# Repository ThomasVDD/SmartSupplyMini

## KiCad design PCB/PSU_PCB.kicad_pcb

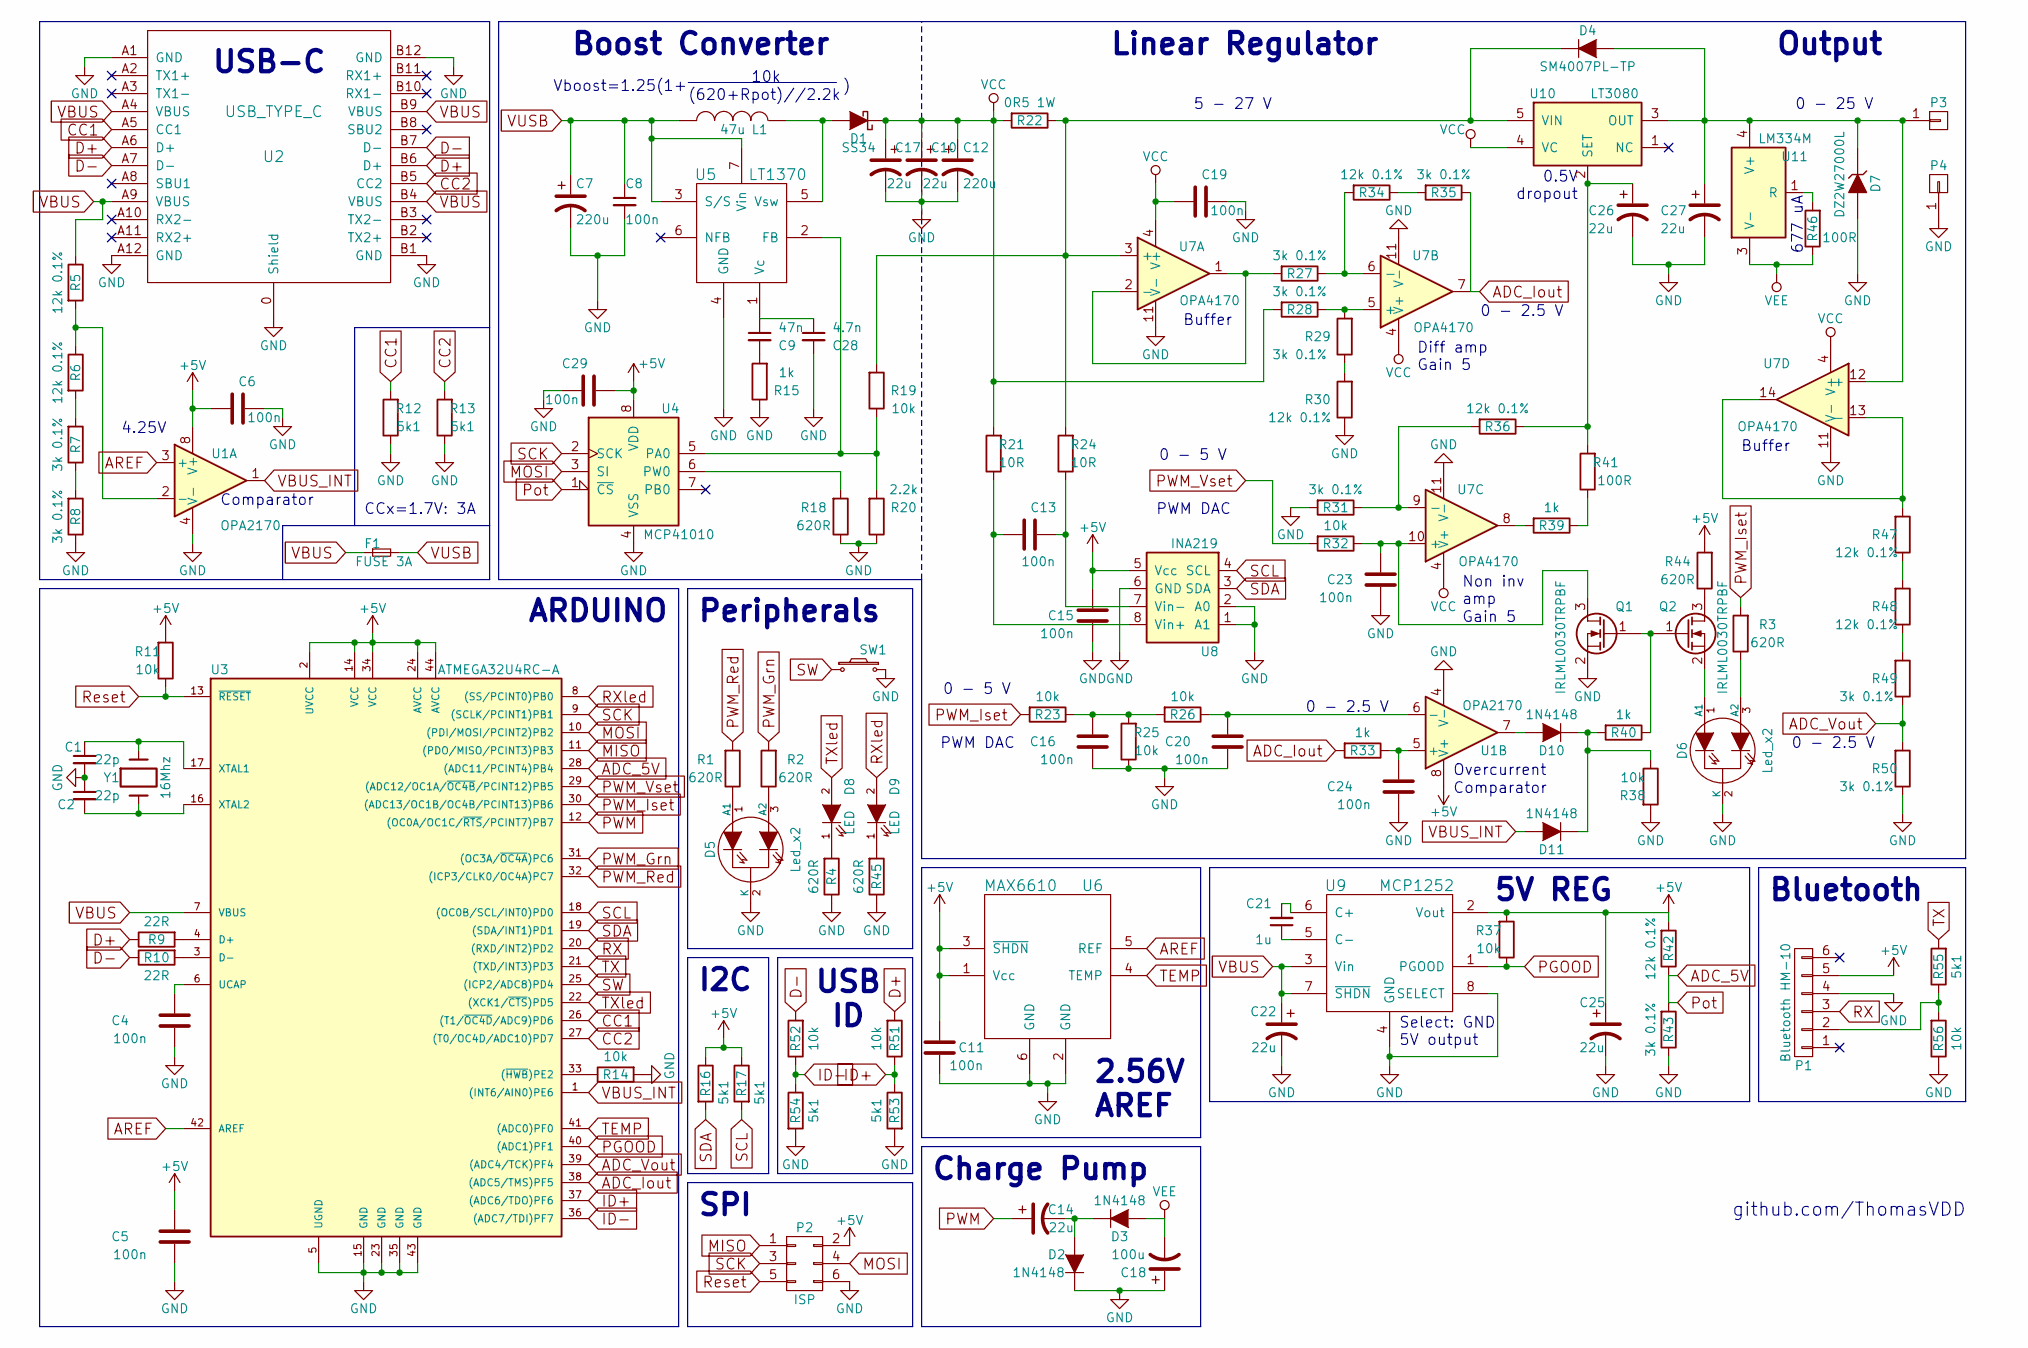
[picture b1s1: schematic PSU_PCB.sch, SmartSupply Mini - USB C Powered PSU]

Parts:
C1, C2: 22p; C_0603_HandSoldering
C4, C5, C6, C8, C11, C13, C15, C16, C19, C20, C23, C24, C29: 100n; C_0603_HandSoldering
C7, C12: 220u; CP_Elec_6.3x7.7
C9: 47n; C_0603_HandSoldering
C10, C17, C27: 22u; CP_Tantalum_Case-V_EIA-7343-20_Hand
C14: 22u; CP_Elec_6.3x7.7
C18: 100u; CP_Elec_6.3x7.7
C21: 1u; C_0603_HandSoldering
C22, C25, C26: 22u; C_0805_HandSoldering
C28: 4.7n; C_0603_HandSoldering
D1: SS34; D_SMC_Handsoldering
D2, D3, D10, D11: 1N4148; D_SOD-323_HandSoldering
D4: SM4007PL-TP; D_SOD-123F
D5, D6: Led_x2; LED_Rectangular_W5.0mm_H2.0mm-3pins
D7: DZ2W27000L; D_SOD-123F
D8, D9: LED; LED_0603_HandSoldering
F1: FUSE 3A; R_0603_HandSoldering
L1: 47u; SELF-WE-PD-XXL
P1: Bluetooth HM-10; Pin_Header_Straight_1x06_Pitch2.54mm
P2: ISP; Pin_Header_Straight_2x03_Pitch2.54mm
P3: V+; BananaPad
P4: V-; BananaPad
Q1, Q2: IRLML0030TRPBF; SOT-23
R1, R2, R3, R4, R18, R44, R45: 620R; R_0603_HandSoldering
R5, R6, R30, R34, R36, R42, R47, R48: 12k 0.1%; R_0603_HandSoldering
R7, R8, R27, R28, R29, R31, R35, R43, R49, R50: 3k 0.1%; R_0603_HandSoldering
R9, R10: 22R; R_0603_HandSoldering
R11, R14, R19, R23, R25, R26, R32, R37, R38, R51, R52, R56: 10k; R_0603_HandSoldering
R12, R13, R16, R17, R53, R54, R55: 5k1; R_0603_HandSoldering
R15, R33, R39, R40: 1k; R_0603_HandSoldering
R20: 2.2k; R_0603_HandSoldering
R21, R24: 10R; R_0603_HandSoldering
R22: 0R5 1W; R_2512_HandSoldering
R41, R46: 100R; R_0603_HandSoldering
SW1: SW_PUSH_SMALL_H; SW_Tactile_SKHH_Angled
U1: OPA2170; SOIC-8_3.9x4.9mm_Pitch1.27mm
U2: USB_TYPE_C; USB_C_Connector
U3: ATMEGA32U4RC-A; TQFP-44_10x10mm_Pitch0.8mm
U4: MCP41010; SOIC-8_3.9x4.9mm_Pitch1.27mm
U5: LT1370; TO-263-7_TabPin4
U6: MAX6610; SOT-23-6_Handsoldering
U7: OPA4170; SOIC-14_3.9x8.7mm_Pitch1.27mm
U8: INA219; SOIC-8_3.9x4.9mm_Pitch1.27mm
U9: MCP1252; MSOP-8_3x3mm_Pitch0.65mm
U10: LT3080; TO-263-5_TabPin3
U11: LM334M; SOIC-8_3.9x4.9mm_Pitch1.27mm
Y1: 16Mhz; Crystal_SMD_HC49-SD_HandSoldering

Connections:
+5V: C5.2, C6.2, C11.1, C15.1, C25.1, C29.2, P1.5, P2.2, R11.2, R16.1, R17.1, R37.2, R42.2, R44.2, U1.8 (V+), U3.2 (UVCC), U3.14 (VCC), U3.24 (AVCC), U3.34 (VCC), U3.44 (AVCC), U4.8 (VDD), U6.1 (Vcc), U6.3 (~SHDN), U8.5 (Vcc), U9.2 (Vout)
ADC_5V: R42.1, R43.2, U3.28 ((ADC11/PCINT4)PB4), U4.1 (~CS)
ADC_Iout: R33.2, R35.1, U3.38 ((ADC5/TMS)PF5), U7.7
ADC_Vout: R49.1, R50.2, U3.39 ((ADC4/TCK)PF4)
AREF: U1.3 (+), U3.42 (AREF), U6.5 (REF)
CC1: R12.2, U2.A5 (CC1), U3.26 ((T1/~OC4D~/ADC9)PD6)
CC2: R13.2, U2.B5 (CC2), U3.27 ((T0/OC4D/ADC10)PD7)
D+: R9.1, R51.2, U2.A6 (D+), U2.B6 (D+)
D-: R10.1, R52.2, U2.A7 (D-), U2.B7 (D-)
GND: C1.2, C2.1, C4.1, C5.1, C6.1, C7.2, C8.2, C10.2, C11.2, C12.2, C15.2, C16.1, C17.2, C18.1, C19.1, C20.1, C22.2, C23.1, C24.1, C25.2, C26.2, C27.2, C28.2, C29.1, D2.1 (K), D5.2 (K), D6.2 (K), D7.2 (A), P1.4, P2.6, P4.1, Q1.2 (S), R4.1, R8.1, R12.1, R13.1, R14.2, R15.1, R18.1, R20.1, R25.1, R30.1, R31.2, R38.2, R43.1, R45.1, R50.1, R53.2, R54.2, R56.1, SW1.2, U1.4 (V-), U2.0 (Shield), U2.A1 (GND), U2.A12 (GND), U2.B1 (GND), U2.B12 (GND), U3.5 (UGND), U3.15 (GND), U3.23 (GND), U3.35 (GND), U3.43 (GND), U4.4 (VSS), U5.4 (GND), U6.2 (GND), U6.6 (GND), U7.11 (V-), U8.1 (A1), U8.2 (A0), U8.6 (GND), U9.4 (GND), U9.8 (SELECT)
ID+: R51.1, R53.1, U3.37 ((ADC6/TDO)PF6)
ID-: R52.1, R54.1, U3.36 ((ADC7/TDI)PF7)
MISO: P2.1, U3.11 ((PDO/MISO/PCINT3)PB3)
MOSI: P2.4, U3.10 ((PDI/MOSI/PCINT2)PB2), U4.3 (SI)
unnamed: C1.1, U3.17 (XTAL1), Y1.1
unnamed: C2.2, U3.16 (XTAL2), Y1.2
unnamed: C4.2, U3.6 (UCAP)
unnamed: C9.2, R15.2
unnamed: C13.1, R24.1, U8.7 (Vin-)
unnamed: C13.2, R21.1, U8.8 (Vin+)
unnamed: C14.2, D2.2 (A), D3.1 (K)
unnamed: C16.2, R23.1, R25.2, R26.2
unnamed: C20.2, R26.1, U1.6 (-)
unnamed: C21.1, U9.5 (C-)
unnamed: C21.2, U9.6 (C+)
unnamed: C23.2, Q1.3 (D), R32.1, U7.10 (+)
unnamed: C24.2, R33.1, U1.5 (+)
unnamed: C26.1, R36.1, R41.2, U10.2 (SET)
unnamed: C27.1, D4.2 (A), D7.1 (K), P3.1, U7.12 (+), U10.3 (OUT), U11.4 (V+)
unnamed: C9.1, C28.1, U5.1 (Vc)
unnamed: D1.2 (A), L1.1, U5.5 (Vsw)
unnamed: D4.1 (K), R19.2, R22.1, R24.2, U7.3 (+), U10.5 (VIN)
unnamed: D5.1 (A1), R1.1
unnamed: D5.3 (A2), R2.1
unnamed: D6.1 (A1), Q2.2 (S)
unnamed: D6.3 (A2), R3.1
unnamed: D8.1 (K), R4.2
unnamed: D9.1 (K), R45.2
unnamed: D10.1 (K), D11.1 (K), R38.1, R40.2
unnamed: D10.2 (A), U1.7
unnamed: P1.2, R55.1, R56.2
unnamed: Q1.1 (G), Q2.1 (G), R40.1
unnamed: Q2.3 (D), R44.1
unnamed: R5.2, R6.1, U1.2 (-)
unnamed: R6.2, R7.2
unnamed: R7.1, R8.2
unnamed: R9.2, U3.4 (D+)
unnamed: R10.2, U3.3 (D-)
unnamed: R14.1, U3.33 ((~HWB~)PE2)
unnamed: R18.2, U4.6 (PW0)
unnamed: R19.1, R20.2, U4.5 (PA0), U5.2 (FB)
unnamed: R27.1, R34.2, U7.6 (-)
unnamed: R27.2, U7.1, U7.2 (-)
unnamed: R28.1, R29.2, U7.5 (+)
unnamed: R29.1, R30.2
unnamed: R31.1, R36.2, U7.9 (-)
unnamed: R34.1, R35.2
unnamed: R39.1, R41.1
unnamed: R39.2, U7.8
unnamed: R46.2, U11.1 (R)
unnamed: R47.1, R48.2
unnamed: R47.2, U7.13 (-), U7.14
unnamed: R48.1, R49.2
PGOOD: R37.1, U3.40 ((ADC1)PF1), U9.1 (PGOOD)
PWM: C14.1, U3.12 ((OC0A/OC1C/~RTS~/PCINT7)PB7)
PWM_Grn: R2.2, U3.31 ((OC3A/~OC4A~)PC6)
PWM_Iset: R3.2, R23.2, U3.30 ((ADC13/OC1B/OC4B/PCINT13)PB6)
PWM_Red: R1.2, U3.32 ((ICP3/CLK0/OC4A)PC7)
PWM_Vset: R32.2, U3.29 ((ADC12/OC1A/~OC4B~/PCINT12)PB5)
RX: P1.3, U3.20 ((RXD/INT2)PD2)
RXled: D9.2 (A), U3.8 ((SS/PCINT0)PB0)
Reset: P2.5, R11.1, U3.13 (~RESET~)
SCK: P2.3, U3.9 ((SCLK/PCINT1)PB1), U4.2 (SCK)
SCL: R17.2, U3.18 ((OC0B/SCL/INT0)PD0), U8.4 (SCL)
SDA: R16.2, U3.19 ((SDA/INT1)PD1), U8.3 (SDA)
SW: SW1.1, U3.25 ((ICP2/ADC8)PD4)
TEMP: U3.41 ((ADC0)PF0), U6.4 (TEMP)
TX: R55.2, U3.21 ((TXD/INT3)PD3)
TXled: D8.2 (A), U3.22 ((XCK1/~CTS~)PD5)
VBUS: C22.1, F1.1, R5.1, U2.A4 (VBUS), U2.A9 (VBUS), U2.B4 (VBUS), U2.B9 (VBUS), U3.7 (VBUS), U9.3 (Vin), U9.7 (~SHDN)
VBUS_INT: D11.2 (A), U1.1, U3.1 ((INT6/AIN0)PE6)
VCC: C10.1, C12.1, C17.1, C19.2, D1.1 (K), R21.2, R22.2, R28.2, U7.4 (V+), U10.4 (VC)
VEE: C18.2, D3.2 (A), R46.1, U11.3 (V-)
VUSB: C7.1, C8.1, F1.2, L1.2, U5.3 (S/S), U5.7 (Vin)

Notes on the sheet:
677 uA
Charge Pump
5V REG
0 - 5 V
0 - 2.5 V
Buffer
Diff amp Gain 5
Comparator
PWM DAC
Non inv amp
Gain 5
0 - 25 V
5 - 27 V
Boost Converter
github.com/ThomasVDD
Vboost=1.25(1+ )
10k
(620+Rpot)//2.2k
__________________
USB-C
ARDUINO
I2C
SPI
Select: GND 5V output
2.56V AREF
Linear Regulator
Output
Peripherals
4.25V
Bluetooth
USB ID
CCx=1.7V: 3A
Overcurrent
0.5V dropout

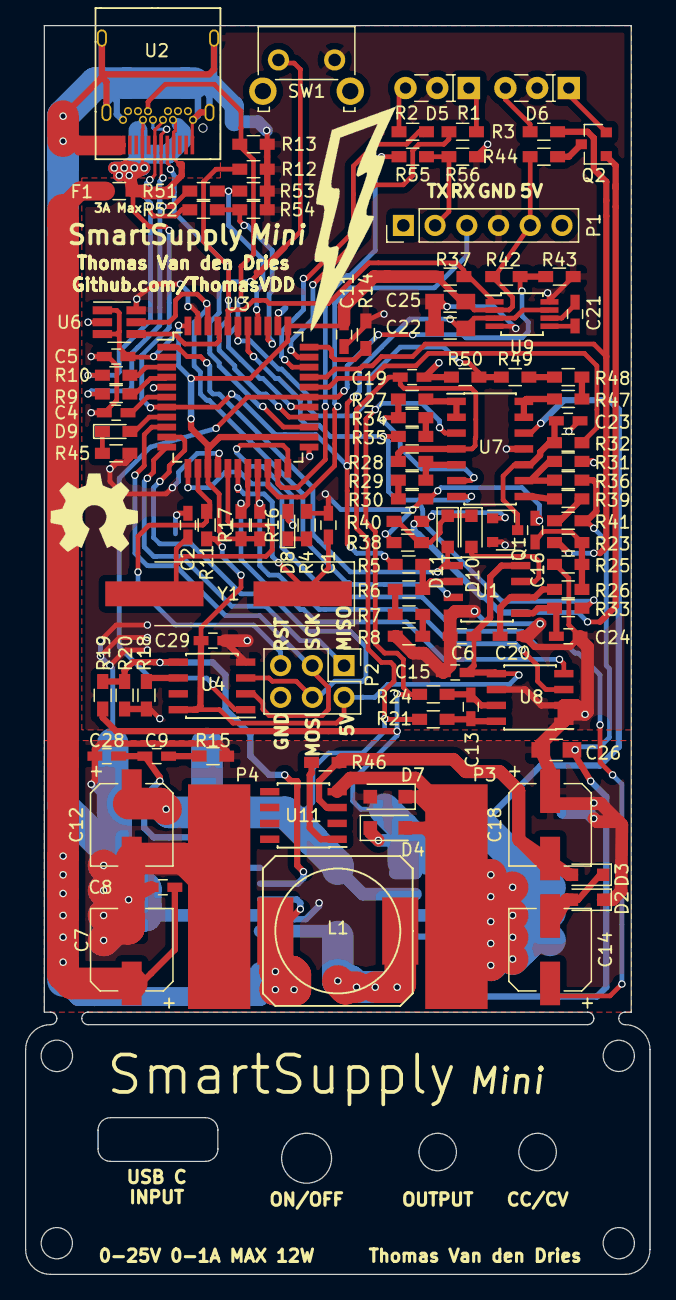
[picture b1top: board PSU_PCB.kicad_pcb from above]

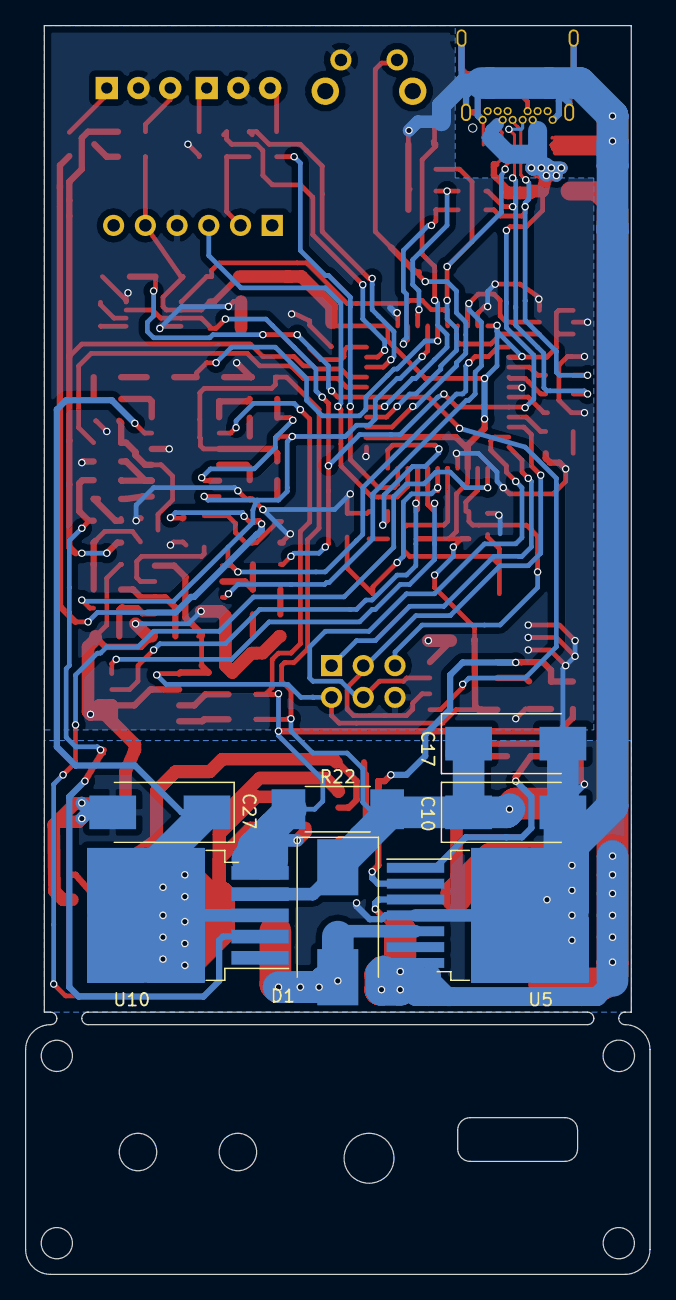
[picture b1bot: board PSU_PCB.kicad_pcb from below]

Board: 2 copper layers, 50.0 x 100.0 mm, 116 parts (7 on the bottom side), 84 nets.

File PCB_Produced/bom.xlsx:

Reference | Amount | Value | Footprint | Price/unit | Price total
Capacitors
C3, 4, 5, 6, 8, 11, 13, 15 16, 19, 20, 23, 24, 29 | 14 | 100n | Capacitors_SMD:C_0603_HandSoldering |  | 0
C22, 25, 26 | 3 | 22u | Capacitors_SMD:C_0805_HandSoldering |  | 0
C1, 2 | 2 | 22p | Capacitors_SMD:C_0603_HandSoldering |  | 0
C28 | 1 | 4.7n | Capacitors_SMD:C_0603_HandSoldering |  | 0
C9 | 1 | 47n | Capacitors_SMD:C_0603_HandSoldering |  | 0
C21 | 1 | 1u | Capacitors_SMD:C_0603_HandSoldering |  | 0
C7, 12, 14, 18 | 4 | 100u | Capacitors_SMD:CP_Elec_6.3x7.7 | 0.25 | 1 | x | http://be.farnell.com/panasonic-electronic-components/eeefk1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
C10, 17, 27 | 3 | 22u | Capacitors_Tantalum_SMD:CP_Tantalum_Case-V_EIA-7343-20_Hand | 1.1399999999999999 | 3.42 | x | http://be.farnell.com/vishay/293d226x9035d2te3/cap-tant-22uf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
 |  |  |  |  | 0
Resistors |  |  |  |  | 0
 |  |  |  |  | 0
R11, 14, 19, 23, 25, 26, 32, 37, 38, 51, 52, 56 | 12 | 10k | Resistors_SMD:R_0603_HandSoldering |  | 0
R7, 8, 27, 28, 29, 31, 35, 43, 49, 50 | 10 | 3k 0.1% | Resistors_SMD:R_0603_HandSoldering | 0.20899999999999999 | 2.09 | x | http://be.farnell.com/panasonic-electronic-components/era3ae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
R5, 6, 30, 34, 36, 42, 47, 48 | 8 | 12k 0.1% | Resistors_SMD:R_0603_HandSoldering | 0.307 | 2.456 | x | http://be.farnell.com/panasonic-electronic-components/era3ae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
R12, 13, 16, 17, 53, 54, 55 | 7 | 5k1 | Resistors_SMD:R_0603_HandSoldering |  | 0
R1, 2, 3, 4, 18, 44, 45 | 7 | 620R | Resistors_SMD:R_0603_HandSoldering |  | 0
R15, 33, 39, 40 | 4 | 1k | Resistors_SMD:R_0603_HandSoldering |  | 0
R21, 24 | 2 | 10R | Resistors_SMD:R_0603_HandSoldering |  | 0
R9, 10 | 2 | 22R | Resistors_SMD:R_0603_HandSoldering |  | 0
R41, 46 | 2 | 100R | Resistors_SMD:R_0603_HandSoldering |  | 0
R20 | 1 | 2.2k | Resistors_SMD:R_0603_HandSoldering |  | 0
R22 | 1 | 0R5 1W | Resistors_SMD:R_2512_HandSoldering | 1.1200000000000001 | 1.1200000000000001 | x | http://be.farnell.com/vishay/wslt2512r5000fea/res-metal-stri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
 |  |  |  |  | 0
Diodes |  |  |  |  | 0
 |  |  |  |  | 0
D5, 6 | 2 | Led_x2 | LEDs:LED_Rectangular_W5.0mm_H2.0mm-3pins | 0.33500000000000002 | 0.67 | x | http://be.farnell.com/kingbright/l-130wdt-1egw/housing-led-w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
D8, 9 | 2 | LED | LEDs:LED_0603_HandSoldering | 4.8500000000000001E-2 | 9.7000000000000003E-2 | x | http://be.farnell.com/kingbright/kpt-1608yc/led-0603-yellow-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
D2, 3, 10, 11 | 4 | 1N4148 | Diodes_SMD:D_SOD-323_HandSoldering | 5.9200000000000003E-2 | 0.23680000000000001 | x | http://be.farnell.com/multicomp/1n4148ws/diode-h-speed-100v-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
D1 | 1 | SS34 | Diodes_SMD:D_SMB_Handsoldering | 0.47199999999999998 | 0.47199999999999998 | x | http://be.farnell.com/on-semiconductor-fairchild/ss34/diode-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
D4 | 1 | SM4007PL-TP | Diodes_SMD:D_SOD-123F | 0.89100000000000001 | 0.89100000000000001 | x | http://be.farnell.com/micro-commercial-components/sm4007pl-t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
D7 | 1 | DZ2W27000L | Diodes_SMD:D_SOD-123F | 0.55500000000000005 | 0.55500000000000005 | x | http://be.farnell.com/panasonic-electronic-components/dz2w27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
 |  |  |  |  | 0
Other |  |  |  |  | 0
 |  |  |  |  | 0
F1 | 1 | FUSE 3A | Resistors_SMD:R_0603_HandSoldering | 0.26 | 0.26 | x | http://be.farnell.com/vishay/mfu0603ff03150p100/fuse-0603-sm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
L1 | 1 | 47u | Inductors:SELF-WE-PD-XXL | 0.5 | 0.5
P1 | 1 | Bluetooth HM-10 | Pin_Headers:Pin_Header_Straight_1x06_Pitch2.54mm | 4 | 4
P2 | 1 | ISP | Pin_Headers:Pin_Header_Straight_2x03_Pitch2.54mm |  | 0
P3 | 1 | V+ | .pretty:BananaPad |  | 0
P4 | 1 | V- | .pretty:BananaPad |  | 0
Q1, 2 | 2 | IRLML0030TRPBF | TO_SOT_Packages_SMD:SOT-23 | 0.28299999999999997 | 0.56599999999999995 | x | http://be.farnell.com/infineon/irlml0030trpbf/mosfet-n-ch-30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
SW1 | 1 | SW_PUSH_SMALL_H | Buttons_Switches_ThroughHole:SW_Tactile_SKHH_Angled |  | 0
U1 | 1 | OPA2170 | Housings_SOIC:SOIC-8_3.9x4.9mm_Pitch1.27mm | 2.13 | 2.13 | x | http://be.farnell.com/texas-instruments/opa2170aid/op-amp-du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
U10 | 1 | LT3080 | TO_SOT_Packages_SMD:TO-263-5_TabPin3 | 4.17 | 4.17 | x | http://be.farnell.com/linear-technology/lt3080eq-pbf/ldo-reg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
U11 | 1 | LM334M | Housings_SOIC:SOIC-8_3.9x4.9mm_Pitch1.27mm | 0.874 | 0.874 | x | http://be.farnell.com/texas-instruments/lm334m-nopb/ic-adj-c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
U2 | 1 | USB_TYPE_C | .pretty:USB_C_Connector | 1.55 | 1.55 | x | http://be.farnell.com/amphenol-commercial-products/12401548e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
U3 | 1 | ATMEGA32U4RC-A | Housings_QFP:TQFP-44_10x10mm_Pitch0.8mm | 3.63 | 3.63 | x | http://be.farnell.com/microchip/atmega32u4-au/mcu-8bit-megaa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
U4 | 1 | MCP41010 | Housings_SOIC:SOIC-8_3.9x4.9mm_Pitch1.27mm | 1.23 | 1.23 | x | http://be.farnell.com/microchip/mcp41010-i-sn/digital-pot-sp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
U5 | 1 | LT1370 | TO_SOT_Packages_SMD:TO-263-7_TabPin4 | 8.92 | 8.92 | x | http://be.farnell.com/linear-technology/lt1370hvir-pbf/switc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
U6 | 1 | MAX6610 | TO_SOT_Packages_SMD:SOT-23-6_Handsoldering | 2.08 | 2.08 | x | http://be.farnell.com/maxim-integrated-products/max6610aut-t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
U7 | 1 | OPA4170 | Housings_SOIC:SOIC-14_3.9x8.7mm_Pitch1.27mm | 2.89 | 2.89 | x | http://be.farnell.com/texas-instruments/opa4170aidr/op-amp-q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
U8 | 1 | INA219 | Housings_SOIC:SOIC-8_3.9x4.9mm_Pitch1.27mm | 2.54 | 2.54 | x | http://be.farnell.com/texas-instruments/ina219bidr/current-p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
U9 | 1 | MCP1252 | Housings_SSOP:MSOP-8_3x3mm_Pitch0.65mm | 1.27 | 1.27 | x | http://be.farnell.com/microchip/mcp1252-33x50i-ms/ic-charge-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
Y1 | 1 | 16Mhz | Crystals:Crystal_SMD_HC49-SD_HandSoldering | 0.30099999999999999 | 0.30099999999999999 | x | http://be.farnell.com/fox-electronics/foxsdlf-160-20/crystal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
 |  |  |  |  | 49.918799999999997
 |  |  |  | BTW | 0.21
 |  |  |  | Total | 60.401747999999998
 |  |  |  | PCB | 36
 |  |  |  | Shipping | 18
 |  |  |  | Import | 25
 |  |  |  | Total | 79
 |  |  |  | Total | 99.901747999999998

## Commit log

2018-04-27 Removed unnecessary files
2018-04-27 Fixed license
2018-06-18 Added libraries
2018-08-09 Fixed minor PCB error Adjusted code for current measurement

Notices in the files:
PCB/PSU_PCB.sch:
Copyright Thomas Van den Dries 2017
